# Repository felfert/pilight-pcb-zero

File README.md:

# pilight-pcb-zero

A minimalistic pcb for connecting a receiver and transmitter for pilight to a Raspberry PI Zero WH.

Parts:

- PCB: See e.g.: https://aisler.net/p/JOIFAOLQ
- Aurel RX-4M50RR30SF: See e.g.: https://www.amazon.de/s?k=RX-4M50RR30SF
- NoName China TX 433Mhz: https://www.amazon.de/Anpro-Empf%C3%A4nger-Superregeneration-Transmitter-Einbrecher/dp/B071J2Z3YK/ref=sr_1_3?__mk_de_DE=%C3%85M%C3%85%C5%BD%C3%95%C3%91&dchild=1&keywords=433Mhz+Transmitter&qid=1596233089&s=ce-de&sr=1-3 (Throw away the receivers, those are crap)
- 13x2 PIN Socket: See e.g.: https://www.reichelt.de/2x13pol-buchsenl-gerade-rm-2-54-h-8-5mm-bl-2x13g8-2-54-p51834.html
- 4x2 PIN Socket: See e.g.: https://www.reichelt.de/rnd-stiftleiste-8-pol-rm-2-54-mm-rnd-205-00635-p208861.html?&nbc=1
- R1, R3, R4, R5: 1k
- R2: 1M potentiometer: See e.g.: https://www.reichelt.de/spindeltrimmer-25-gaenge-1-mohm-linear-vis-m64y105kb40-p238621.html?&nbc=1
- 2 Antennas: See e.g.: https://www.amazon.de/gp/product/B07FYX7WBW/ref=ppx_yo_dt_b_asin_title_o06_s00

Notes:

 - J1 is placed on the opposite side of the PCB
 - The second Antenna cable is connected directly to the TX-Module.
 - There is a sqare solder mask for GND of the RX-Antenna on the HAT PCB near U2.

 J2 and the corresponding R3 - R5 implement the following optional additional features

   Power button
   Power LED
   Wifi LED
   TX LED

   For these, additional scripts resp. configuration is required which can be found in the custom/ subdir.

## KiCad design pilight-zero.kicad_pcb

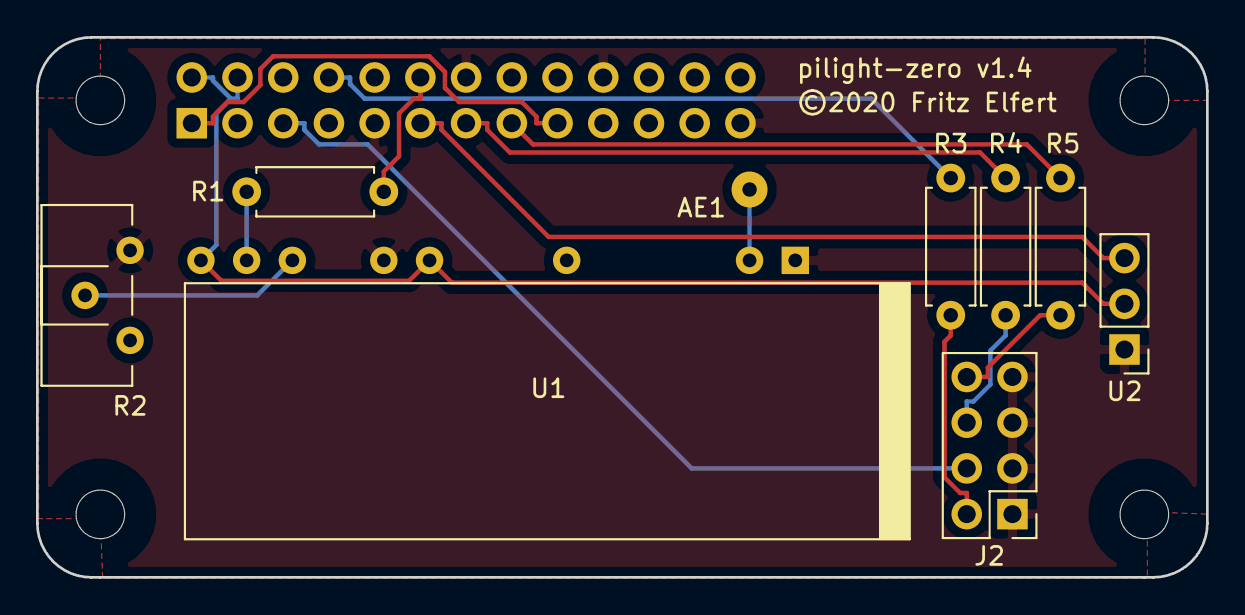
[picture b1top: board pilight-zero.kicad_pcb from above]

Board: 2 copper layers, 65.0 x 30.0 mm, 14 parts (1 on the bottom side), 15 nets.

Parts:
AE1: Antenna; SolderWirePad_1x01_Drill0.8mm
H1, H2, H3, H4: MountingHole; MountingHole_2.7mm_M2.5_uHAT_RPi
J1: GPIO partial; PinSocket_2x13_P2.54mm_Vertical_Special_Anchor
J2: Conn_02x04_Odd_Even; PinHeader_2x04_P2.54mm_Vertical
R1, R3, R4, R5: 1k; R_Axial_DIN0207_L6.3mm_D2.5mm_P7.62mm_Horizontal
R2: 1M; Potentiometer_ACP_CA9-H2,5_Horizontal
U1: RX-4M50RR30SF
U2: TX_433Mhz; TX-433Mhz

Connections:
+3V3: J1.1, J1.17
+5V: J1.2, J1.4, U1.10, U1.15, U2.2
/GPIO3_SCL1: J1.5, J2.4
/GPIO14_TXD0: J1.8, R3.1
/GPIO17_GEN0: J1.11, U2.3
/GPIO18_GEN1: J1.12, R1.2
/GPIO22_GEN3: J1.15, R5.1
/GPIO27_GEN2: J1.13, R4.1
/PwrLED: J2.2, R3.2
/TxLED: J2.8, R5.2
/WifiLED: J2.6, R4.2
GND: J1.6, J1.9, J1.14, J1.20, J1.25, J2.1, J2.3, J2.5, J2.7, R2.3, U1.2, U1.7, U1.11, U2.1
unnamed: AE1.1, U1.3
unnamed: R1.1, U1.14
unnamed: R2.2, U1.13

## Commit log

2020-06-21 Initial import
2020-06-21 Update Parts list
2020-06-21 Add Note about Antenna 2
2020-06-21 Replaced R2 by pot
2020-06-21 Add 3D model for trimmer
2020-07-31 Misc fixes and additions
    - Fixed pad dimensions of potentiometer
    - Added pinheader and resistors for
    - Power button
    - Power LED
    - Wifi LED
    - 433Mhz TX LED
2020-08-01 Updated misc 3d models
2020-08-01 Changed WifiLED output to GPIO27
2020-08-01 Bumped silk version number

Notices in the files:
pilight-zero.kicad_pcb:
This PCB design is licensed under MIT Open Source License.
©2020 Fritz Elfert
